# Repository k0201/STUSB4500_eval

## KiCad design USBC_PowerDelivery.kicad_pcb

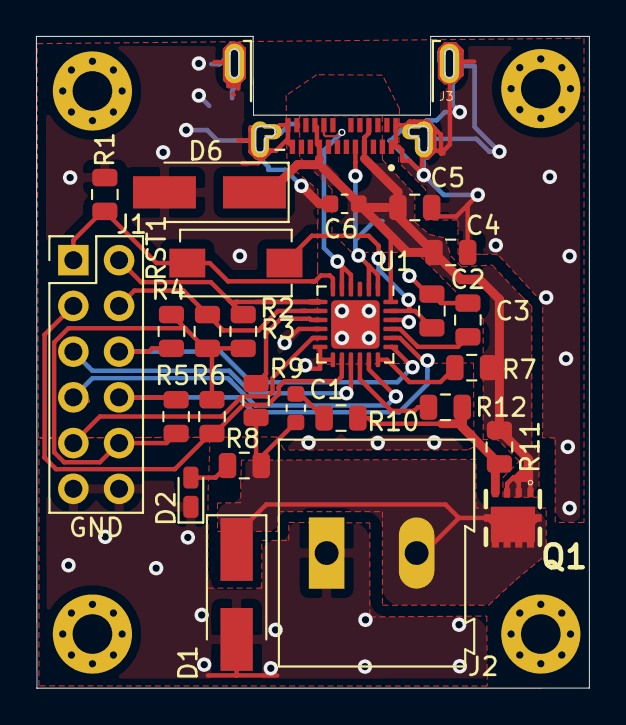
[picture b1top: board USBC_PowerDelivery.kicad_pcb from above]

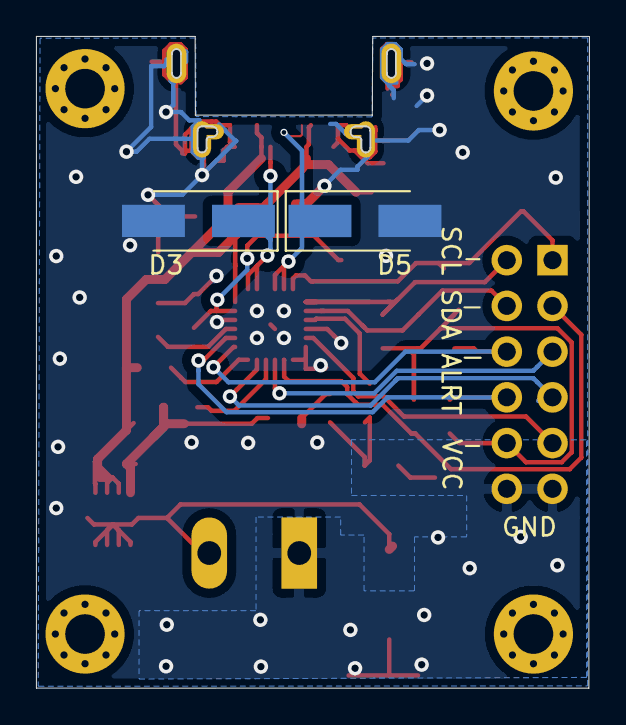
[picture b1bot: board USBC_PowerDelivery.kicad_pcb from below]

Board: 2 copper layers, 30.7 x 36.2 mm, 33 parts (2 on the bottom side), 23 nets.

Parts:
C1: 100N; C_0603_1608Metric
C2, C3, C4, C5: 1u; C_0805_2012Metric
C6: 100n; C_0603_1608Metric
D1, D3, D5, D6: D_TVS; D_SMA_Handsoldering
D2: LED; LED_0603_1608Metric_Castellated
H1, H2, H3, H4: MountingHole; MountingHole_2.2mm_M2_Pad_Via
J1: Conn_02x06_Odd_Even; PinHeader_2x06_P2.54mm_Vertical
J2: Screw_Terminal_01x02; TerminalBlock_Altech_AK300-2_P5.00mm
J3: 1-2295018-2; TE_1-2295018-2
Q1: AON7752; DFN_3X3_EP
R1, R10, R11: 100K; R_0805_2012Metric
R2, R3, R7, R9: 4.7k; R_0805_2012Metric
R4: 10k; R_0805_2012Metric
R5, R6: 100k; R_0805_2012Metric
R8: 2.2k; R_0805_2012Metric
R12: 22K; R_0805_2012Metric
RST1: SW_Push; SW_SPST_EVQPE1
U1: STUSB4500QTR; QFN-24-1EP_4x4mm_P0.5mm_EP2.7x2.7mm

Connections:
/1V2: C2.1, U1.21
/2V7: C3.2, RST1.2, U1.23
/ALERT: J1.6, R4.1, U1.19
/ATTACH: J1.9, U1.11
/A_B_SIDE: J1.7, U1.17
/CC1: D3.1, J3.A5, U1.1, U1.2
/CC2: D5.1, J3.B5, U1.4, U1.5
/DISCH: R9.1, U1.9
/GPIO: J1.5, U1.15
/POK2: J1.8, R5.2, U1.20
/POK3: J1.3, R6.2, U1.14
/RST: J1.1, R1.1, RST1.1, U1.6
/SCL: J1.2, R3.1, U1.7
/SDA: J1.4, R2.1, U1.8
/vBUS: C4.1, C5.1, C6.1, D6.1, J3.A4, J3.A9, J3.B4, J3.B9, Q1.1, Q1.2, Q1.3, R7.1, R11.1, U1.24
GND: C2.2, C3.1, C4.2, C5.2, C6.2, D1.2, D2.1, D3.2, D5.2, D6.2, J1.11, J1.12, J2.1, J3.A1, J3.A12, J3.B1, J3.B12, J3.P1_1, J3.P1_2, J3.P2_1, J3.P2_2, J3.P4, J3.P5, R1.2, U1.10, U1.12, U1.13, U1.22, U1.25
unnamed: C1.1, D1.1, J2.2, Q1.5, Q1.6, Q1.7, Q1.8, R8.1, R9.2
unnamed: C1.2, R10.2
unnamed: D2.2, R8.2
unnamed: Q1.4, R10.1, R11.2, R12.1
unnamed: R7.2, U1.18
unnamed: R12.2, U1.16
VCC: J1.10, R2.2, R3.2, R4.2, R5.1, R6.1

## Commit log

2019-11-16 initial version of hardware
2019-11-17 added 3d fotprints and cleanup on schematic
